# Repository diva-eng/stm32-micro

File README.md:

# STM32 Micro
A bare minimum implementation for STM32 microcontroller

## Development
TBD

## Schematic

[Schematic Link](./schematic.pdf)

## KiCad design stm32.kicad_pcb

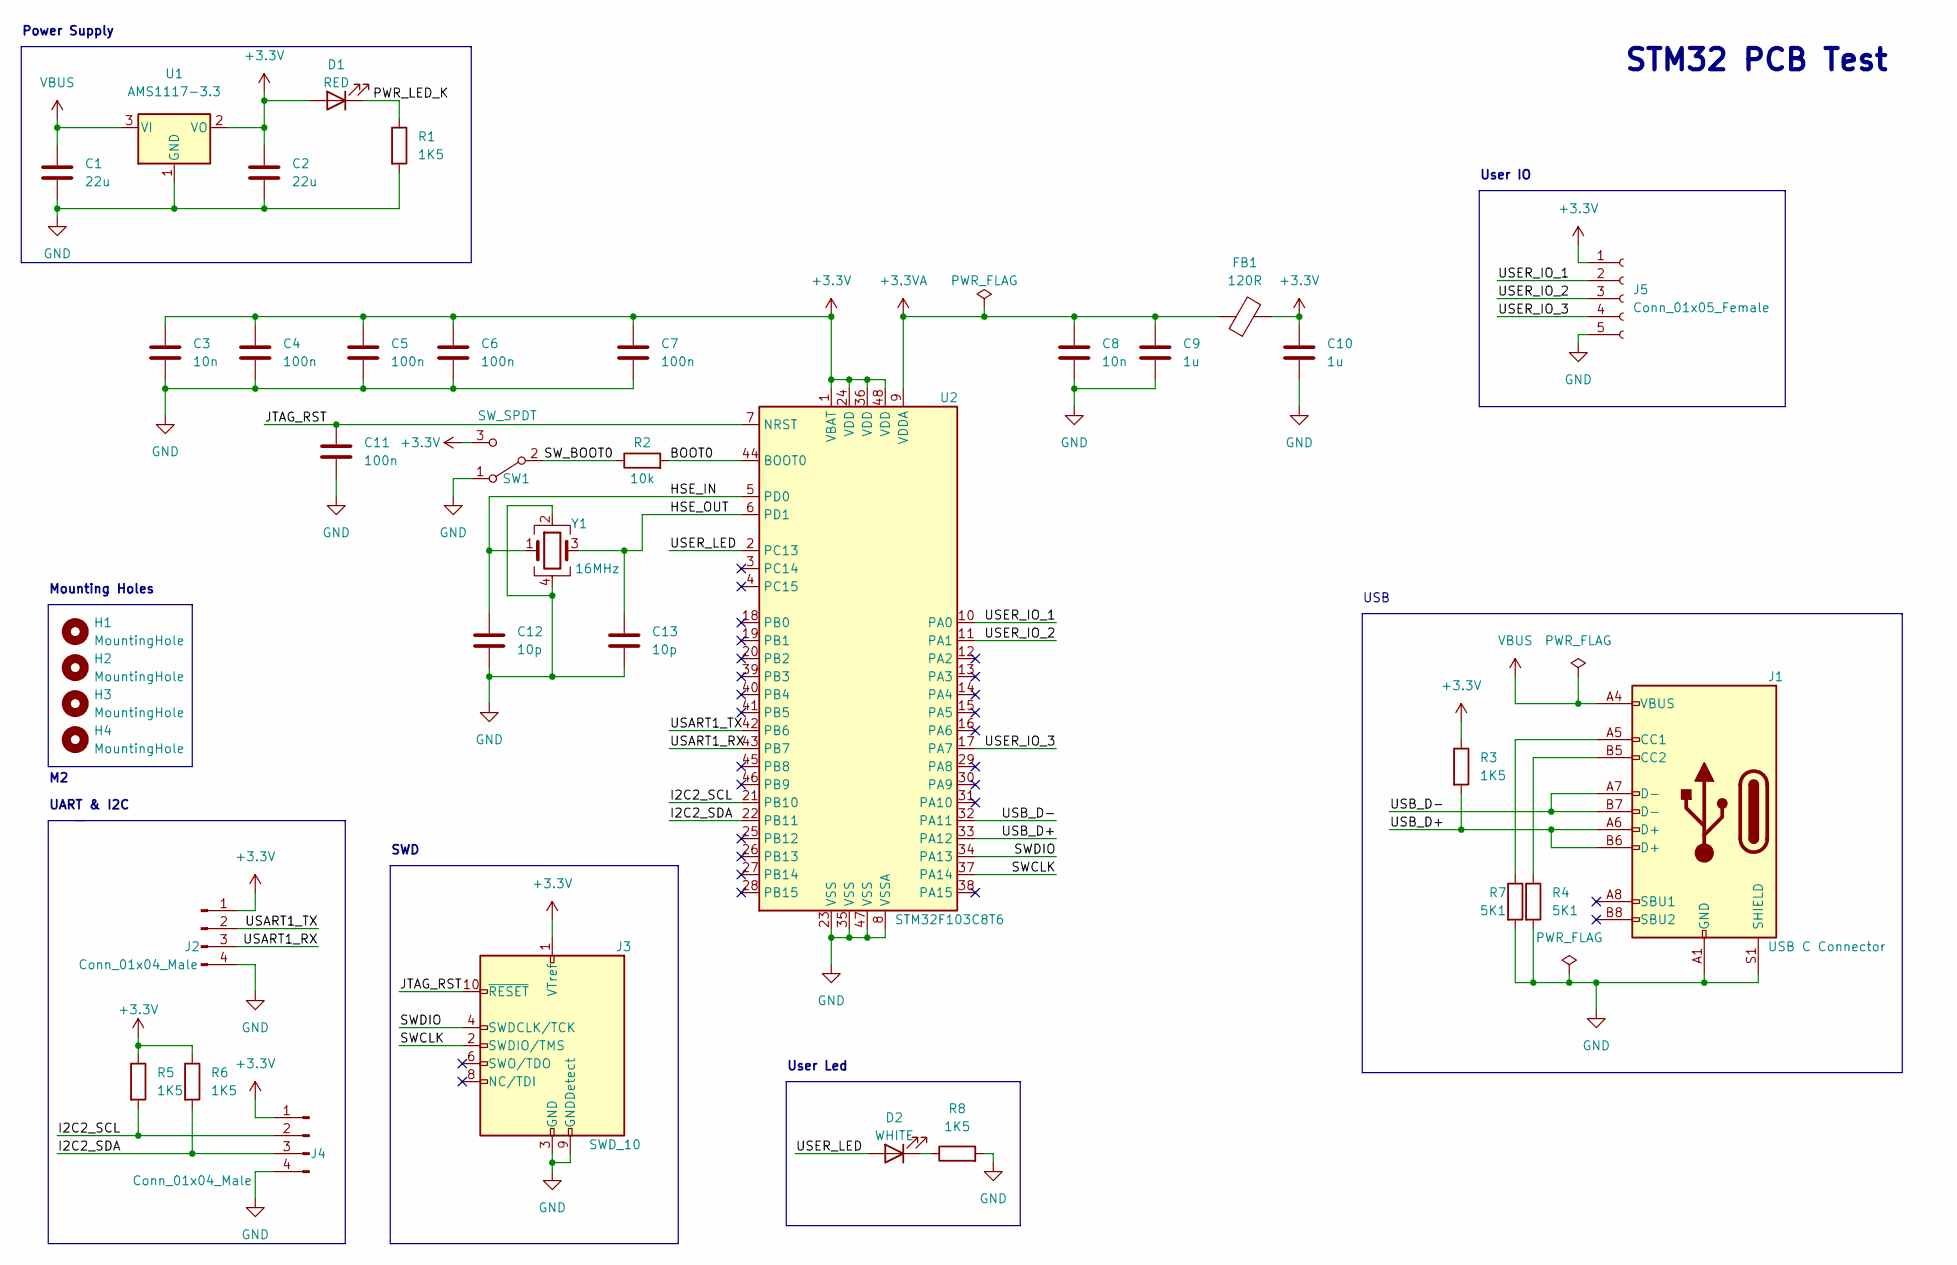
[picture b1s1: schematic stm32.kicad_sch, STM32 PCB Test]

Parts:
C1, C2: 22u; C_0805_2012Metric
C3: 10n; C_0603_1608Metric
C4, C5, C6, C7, C11: 100n; C_0402_1005Metric
C8: 10n; C_0402_1005Metric
C9, C10: 1u; C_0402_1005Metric
C12, C13: 10p; C_0402_1005Metric
D1: RED; LED_0603_1608Metric
D2: WHITE; LED_0603_1608Metric
FB1: 120R; L_0603_1608Metric
H1, H2, H3, H4: MountingHole; MountingHole_2.2mm_M2
J1: USB C Connector; USB_C_Receptacle_Palconn_UTC16-G
J2, J4: Conn_01x04_Male; PinHeader_1x04_P2.54mm_Vertical
J3: SWD_10; PinHeader_2x05_P1.27mm_Vertical_SMD
J5: Conn_01x05_Female; PinSocket_1x05_P2.54mm_Vertical
R1, R3, R5, R6, R8: 1K5; R_0402_1005Metric
R2: 10k; R_0402_1005Metric
R4, R7: 5K1; R_0402_1005Metric
SW1: SW_SPDT; SW_SPDT_PCM12
U1: AMS1117-3.3; SOT-223-3_TabPin2
U2: STM32F103C8T6; LQFP-48_7x7mm_P0.5mm
Y1: 16MHz; Crystal_SMD_3225-4Pin_3.2x2.5mm

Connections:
+3.3VA: C8.1, C9.1, FB1.1, U2.9 (VDDA)
+3V3: C2.1, C3.1, C4.1, C5.1, C6.1, C7.1, C10.1, D1.2 (A), FB1.2, J2.1, J3.1 (VTref), J4.1, J5.1, R3.1, R5.1, R6.1, SW1.3 (C), U1.2 (VO), U2.1 (VBAT), U2.24 (VDD), U2.36 (VDD), U2.48 (VDD)
/BOOT0: R2.2, U2.44 (BOOT0)
/HSE_IN: C12.1, U2.5 (PD0), Y1.1
/HSE_OUT: C13.1, U2.6 (PD1), Y1.3
/I2C2_SCL: J4.2, R5.2, U2.21 (PB10)
/I2C2_SDA: J4.3, R6.2, U2.22 (PB11)
/JTAG_RST: C11.1, J3.10 (~RESET), U2.7 (NRST)
/PWR_LED_K: D1.1 (K), R1.1
/SWCLK: J3.2 (SWDIO/TMS), U2.37 (PA14)
/SWDIO: J3.4 (SWDCLK/TCK), U2.34 (PA13)
/SW_BOOT0: R2.1, SW1.2 (B)
/USART1_RX: J2.3, U2.43 (PB7)
/USART1_TX: J2.2, U2.42 (PB6)
/USB_D+: J1.A6 (D+), J1.B6 (D+), R3.2, U2.33 (PA12)
/USB_D-: J1.A7 (D-), J1.B7 (D-), U2.32 (PA11)
/USER_IO_1: J5.2, U2.10 (PA0)
/USER_IO_2: J5.3, U2.11 (PA1)
/USER_IO_3: J5.4, U2.17 (PA7)
/USER_LED: D2.2 (A), U2.2 (PC13)
GND: C1.2, C2.2, C3.2, C4.2, C5.2, C6.2, C7.2, C8.2, C9.2, C10.2, C11.2, C12.2, C13.2, J1.A1 (GND), J1.A12 (GND), J1.B1 (GND), J1.B12 (GND), J1.S1 (SHIELD), J2.4, J3.3 (GND), J3.5 (GND), J3.9 (GNDDetect), J4.4, J5.5, R1.2, R4.2, R7.2, R8.2, SW1.1 (A), U1.1 (GND), U2.8 (VSSA), U2.23 (VSS), U2.35 (VSS), U2.47 (VSS), Y1.2, Y1.4
unnamed: D2.1 (K), R8.1
unnamed: J1.A5 (CC1), R7.1
unnamed: J1.B5 (CC2), R4.1

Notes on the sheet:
STM32 PCB Test
User Led
User IO
Mounting Holes
Power Supply
USB
UART & I2C
SWD

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
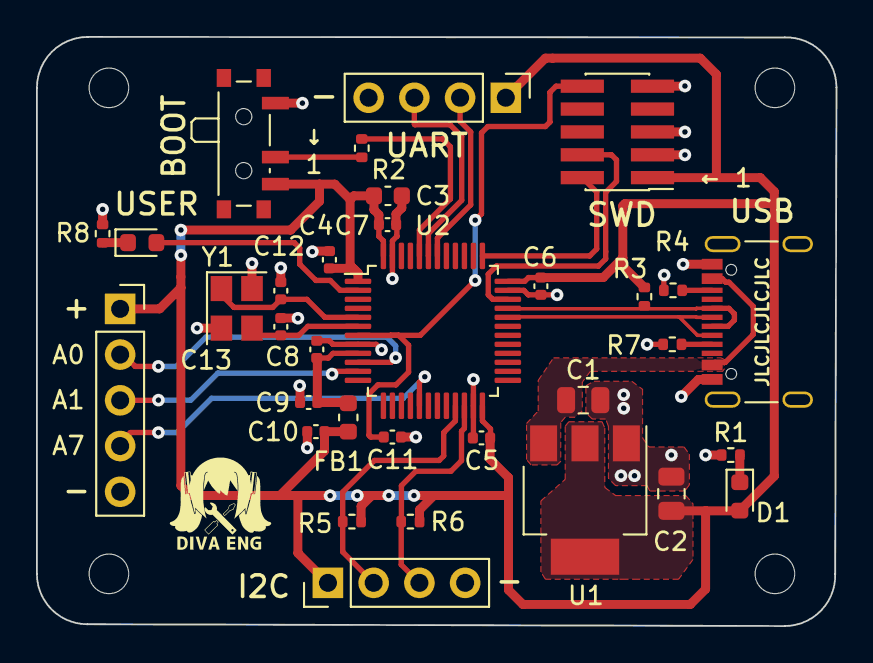
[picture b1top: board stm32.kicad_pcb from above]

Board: 2 copper layers, 44.4 x 32.7 mm, 37 parts (0 on the bottom side), 25 nets.

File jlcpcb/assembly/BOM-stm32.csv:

Comment,Designator,Footprint,LCSC
16MHz,Y1,Crystal_SMD_3225-4Pin_3.2x2.5mm,C112972
SWD_10,J3,PinHeader_2x05_P1.27mm_Vertical_SMD,C150517
10n,C8,C_0402_1005Metric,C15195
100n,"C11,C4,C5,C6,C7",C_0402_1005Metric,C1525
USB C Connector,J1,USB_C_Receptacle_Palconn_UTC16-G,C167321
SW_SPDT,SW1,SW_SPDT_PCM12,C221841
RED,D1,LED_0603_1608Metric,C2286
RED,D2,LED_0603_1608Metric,C2290
10k,R2,R_0402_1005Metric,C25744
1K5,"R1,R3,R5,R6,R8",R_0402_1005Metric,C25867
5K1,"R4,R7",R_0402_1005Metric,C25905
10p,"C12,C13",C_0402_1005Metric,C32949
22u,"C1,C2",C_0805_2012Metric,C45783
120R,FB1,L_0603_1608Metric,C491556
1u,"C10,C9",C_0402_1005Metric,C52923
10n,C3,C_0603_1608Metric,C57112
AMS1117-3.3,U1,SOT-223-3_TabPin2,C6186
STM32F103C8T6,U2,LQFP-48_7x7mm_P0.5mm,C8734

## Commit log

2022-05-29 update infos
